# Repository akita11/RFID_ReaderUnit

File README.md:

# RFID Reader UNIT

## 内容

Felica対応のRFIDリーダICのForSinVe社FSVP532（よく使われるNXP社のPN532互換）を使ったRFIDリーダです。M5Stack等のマイコンとGroveケーブル（I2C通信）で接続して、FelicaやNFCを読み書きすることができます。PN532用のライブラリで使用することができます。（UIFlow用のカスタムブロックを用意する予定）

## 使い方

ArduinoやM5Stack等のマイコンにGroveポート経由でI2C接続します。
ソフトウエアはは、PN532用のもの使用します。
PN532用のソフトウエアとしては、Arduino用ライブラリがいくつかあります。
例えばAdafruitやSeeedのものがありますが、Felicaを読み出す関数とサンプルプログラムは提供されていないようです。
[こちら](https://github.com/elechouse/PN532)のライブラリは、これらを元にしたもの（fork）で、Felica関連の関数やサンプルプログラムも含まれているので、こちらを利用するとよいでしょう。
ただしサンプルプログラムは、PN532をI2C接続して使用する設定にはなっていませんので、冒頭の以下の「※」のところを変更します。これにより、I2C接続で使用できるようになります。
```FeliCa_card_read.pde
#if 0 // <--- ※original:1
  #include <SPI.h>
  #include <PN532_SPI.h>
  #include <PN532.h>

PN532_SPI pn532spi(SPI, 10);
PN532 nfc(pn532spi);
#elif 0
  #include <PN532_HSU.h>
  #include <PN532.h>

PN532_HSU pn532hsu(Serial1);
PN532 nfc(pn532hsu);
#else
  #include <Wire.h>
  #include <PN532_I2C.h>
  #include <PN532.h>

PN532_I2C pn532i2c(Wire);
PN532 nfc(pn532i2c);
#endif
```

なお稀に電源ON時のリセット(POR; Power On Reset)が効かず、初期化に失敗することがあるようです。その場合は、電源を入れなおしてください。

## 電波関連法令の規格について

RFIDリーダは無線通信機器ではなく「誘導式読み書き通信設備」というカテゴリに含まれます。
そのため、無線通信機器の認証に必要な、いわゆる技適は無関係です。
（[法令関連の情報まとめの例](http://dsas.blog.klab.org/archives/2018-04/52291765.html)）
「誘導式読み書き通信設備」は、法令の要件（電界強度の規定、または総務大臣型式指定）を満たせば許可不要で使用することができる、と規定されています。
その要件のうちの「電界強度の規定」（3mの距離における電界強度が500μV/m（≒54dBμV/m）以下）を満たしていることの表示方法については明記されていません。
そのため、測定条件や測定データ等の客観的なデータを示すことで、その要件を満たす、というのが一般的な解釈と考えています。
例えば（株）スイッチサイエンスで販売している[RFID2 Unit](https://www.switch-science.com/products/8301)では、電界強度の測定法・測定結果を示し、それに基づいて規定を満たしている、と表示しています。

このRFID Reader UNITの電界強度測定の測定法・測定結果は「RFID_ReaderUNIT_meaasure.pdf」に記載の通り、これは法令の要件である電界強度の規定を満たしています。
なお今回のアンテナ設計手順をまとめた資料は、AntennaDesign/以下にあります。

## Author

Junichi Akita (@akita11) / akita@ifdl.jp

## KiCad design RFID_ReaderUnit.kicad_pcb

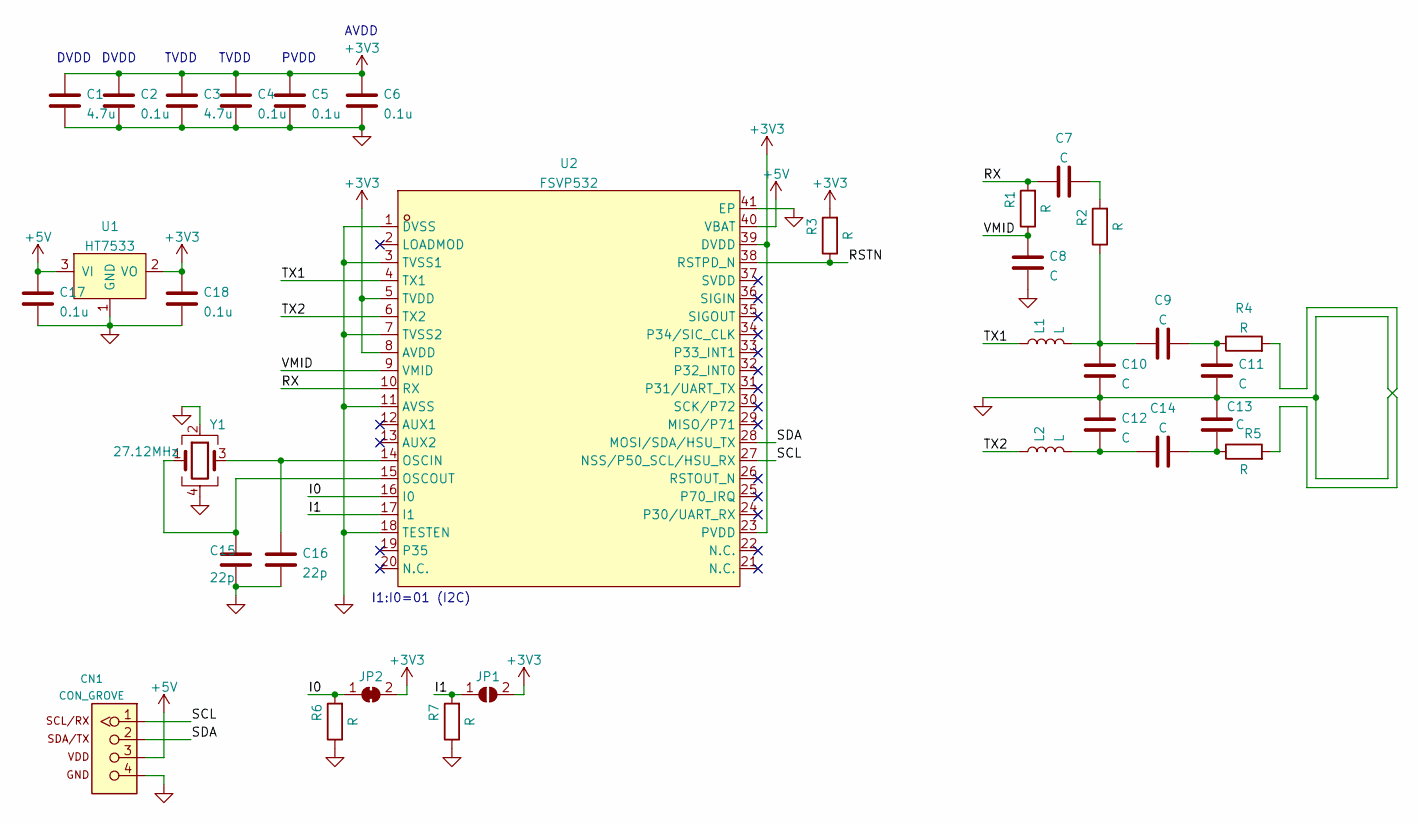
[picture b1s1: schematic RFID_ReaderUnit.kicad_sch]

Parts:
C1, C3: 4.7u; C_0603_1608Metric
C2, C4, C5, C6, C17, C18: 0.1u; C_0603_1608Metric
C7, C8, C9, C10, C11, C12, C13, C14: C; C_0603_1608Metric
C15, C16: 22p; C_0603_1608Metric
CN1: CON_GROVE; CON_GROVE_H
JP1: SolderJumper_2_Open; SolderJumper-2_P1.3mm_Open_Pad1.0x1.5mm
JP2: SolderJumper_2_Bridged; SolderJumper-2_P1.3mm_Bridged_Pad1.0x1.5mm
L1, L2: L; L_0805_2012Metric
R1, R2, R3, R4, R5, R6, R7: R; R_0603_1608Metric
U1: HT7533; SOT-23; LCSC C5136781
U2: FSVP532; QFN-40_L6.0-W6.0-P0.50-TL-EP4.4; LCSC Part C5336464
Y1: 27.12MHz; Crystal_SMD_3225-4Pin_3.2x2.5mm

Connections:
+3V3: C1.1, C2.1, C3.1, C4.1, C5.1, C6.1, C18.1, JP1.2 (B), JP2.2 (B), R3.2, U1.2 (VO), U2.5 (TVDD), U2.8 (AVDD), U2.23 (PVDD), U2.39 (DVDD)
+5V: C17.1, CN1.3, U1.3 (VI), U2.40 (VBAT)
/I0: JP2.1 (A), R6.2, U2.16 (I0)
/I1: JP1.1 (A), R7.2, U2.17 (I1)
/RSTN: R3.1, U2.38 (RSTPD_N)
/RX: C7.1, R1.2, U2.10 (RX)
/SCL: CN1.1, U2.27 (NSS/P50_SCL/HSU_RX)
/SDA: CN1.2, U2.28 (MOSI/SDA/HSU_TX)
/TX1: L1.1, U2.4 (TX1)
/TX2: L2.1, U2.6 (TX2)
/VMID: C8.2, R1.1, U2.9 (VMID)
GND: C1.2, C2.2, C3.2, C4.2, C5.2, C6.2, C8.1, C10.2, C11.2, C12.1, C13.1, C15.2, C16.2, C17.2, C18.2, CN1.4, R4.2, R5.2, R6.1, R7.1, U1.1 (GND), U2.1 (DVSS), U2.3 (TVSS1), U2.7 (TVSS2), U2.11 (AVSS), U2.18 (TESTEN), U2.41 (EP), Y1.2, Y1.4
unnamed: C7.2, R2.2
unnamed: C9.1, C10.1, L1.2, R2.1
unnamed: C9.2, C11.1, R4.1
unnamed: C12.2, C14.1, L2.2
unnamed: C13.2, C14.2, R5.1
unnamed: C15.1, U2.15 (OSCOUT), Y1.1
unnamed: C16.1, U2.14 (OSCIN), Y1.3

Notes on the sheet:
TVDD
PVDD
DVDD
AVDD
I1:I0=01 (I2C)

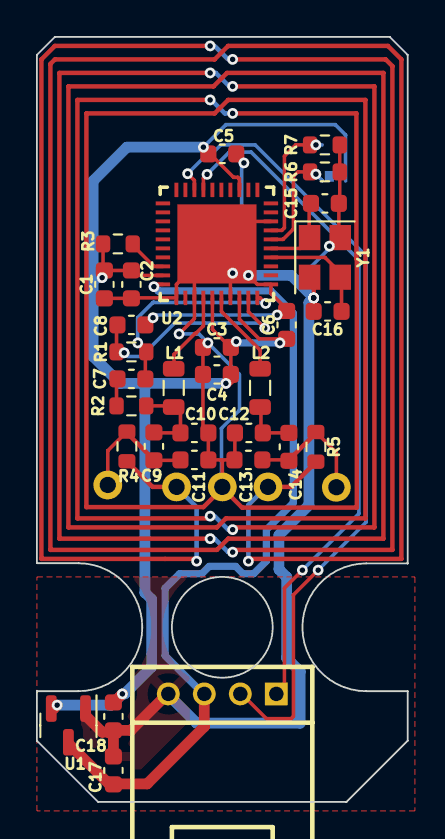
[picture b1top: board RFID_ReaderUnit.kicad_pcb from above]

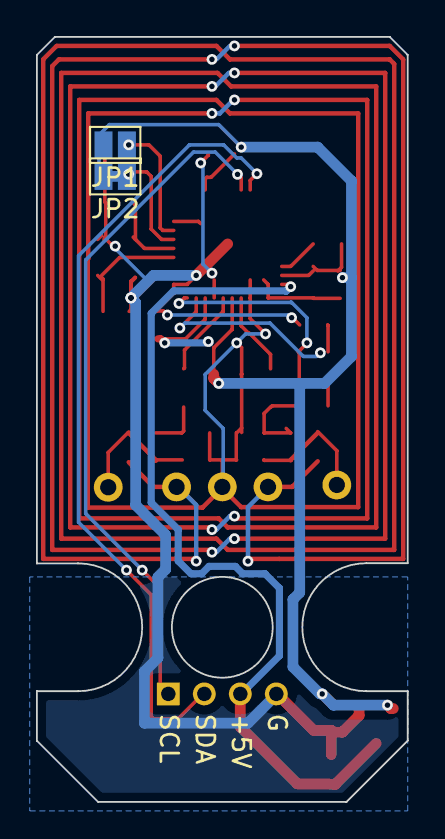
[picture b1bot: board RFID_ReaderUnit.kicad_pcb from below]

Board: 2 copper layers, 20.6 x 42.5 mm, 33 parts (2 on the bottom side), 19 nets.

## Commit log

2025-07-07 URL link typo fix
2025-07-13 add photo
